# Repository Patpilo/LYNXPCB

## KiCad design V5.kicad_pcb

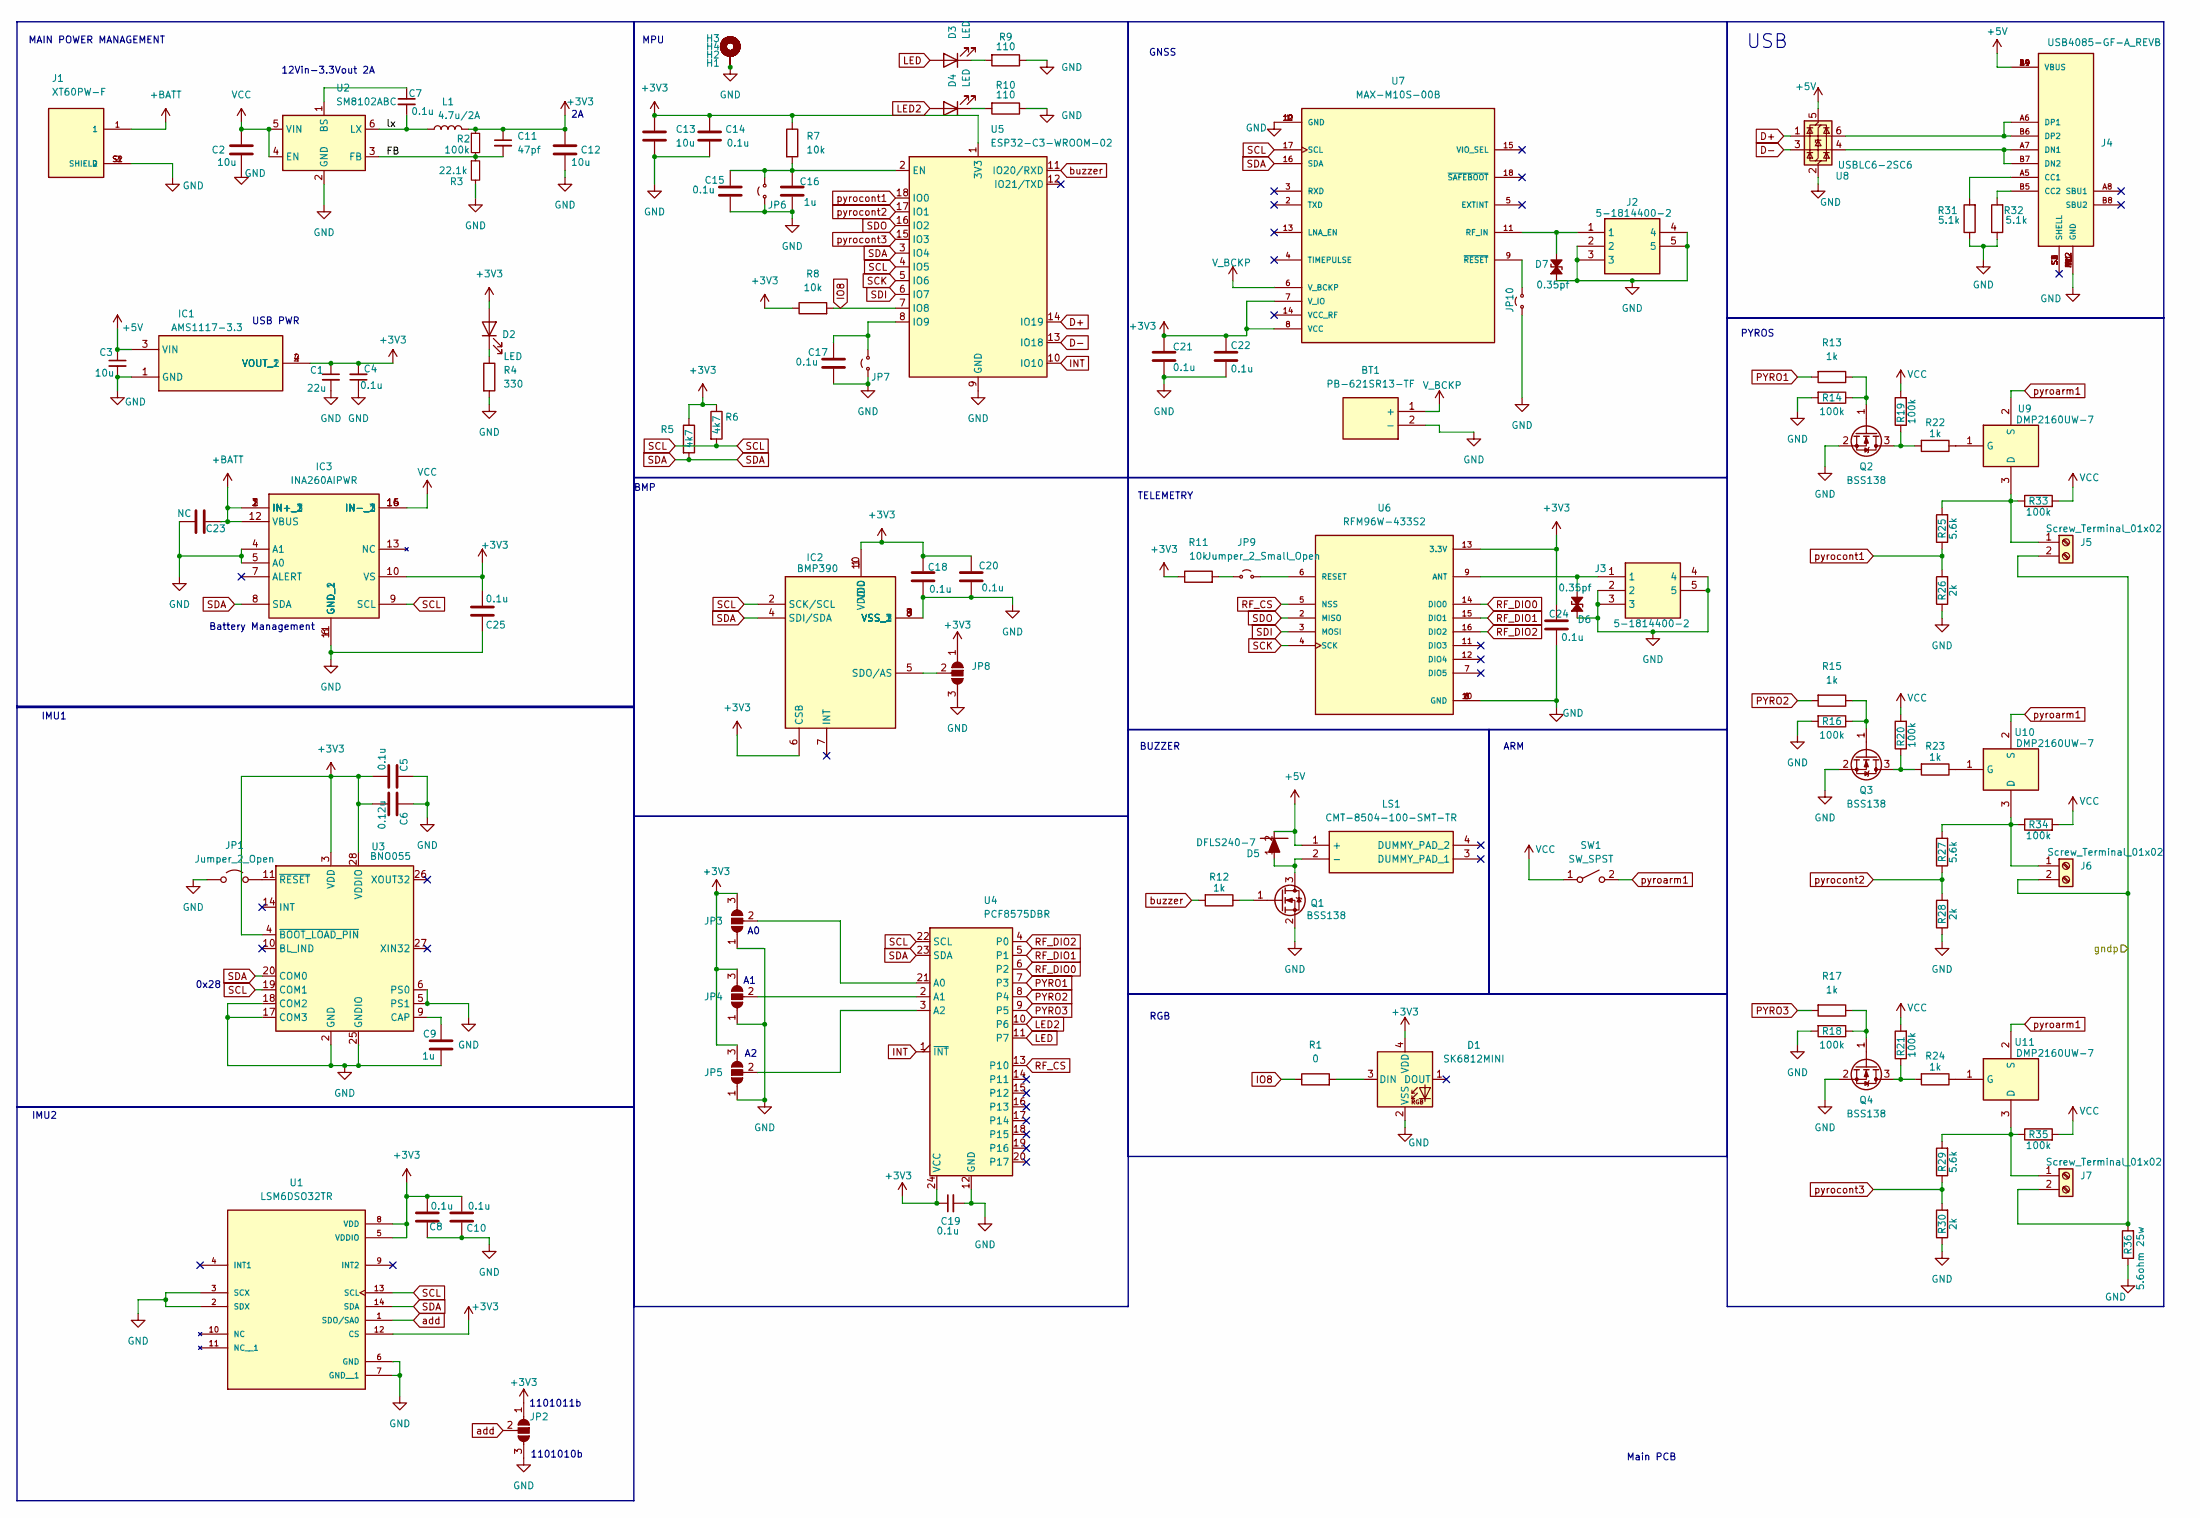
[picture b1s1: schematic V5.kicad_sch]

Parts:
BT1: PB-621SR13-TF; PB621SR13TF; Manufacturer_Part_Number PB-621SR13-TF
C1: 22u; C_0805_2012Metric_Pad1.18x1.45mm_HandSolder
C2, C12: 10u; C_1206_3216Metric_Pad1.33x1.80mm_HandSolder
C3, C13: 10u; C_0805_2012Metric_Pad1.18x1.45mm_HandSolder
C4, C7, C15, C17, C18, C19, C20, C21, C22: 0.1u; C_0805_2012Metric_Pad1.18x1.45mm_HandSolder
C5, C8, C10, C14, C25: 0.1u; C_0201_0603Metric_Pad0.64x0.40mm_HandSolder
C6: 0.12u; C_0201_0603Metric_Pad0.64x0.40mm_HandSolder
C9, C16: 1u; C_0805_2012Metric_Pad1.18x1.45mm_HandSolder
C11: 47pf; C_0402_1005Metric_Pad0.74x0.62mm_HandSolder
C23: NC; C_0201_0603Metric_Pad0.64x0.40mm_HandSolder
C24: 0.1u; C_1206_3216Metric_Pad1.33x1.80mm_HandSolder
D1: SK6812MINI; LED_SK6812MINI_PLCC4_3.5x3.5mm_P1.75mm
D2, D3, D4: LED; LED_0805_2012Metric_Pad1.15x1.40mm_HandSolder
D5: DFLS240-7; POWERDI123; Manufacturer_Part_Number DFLS240-7; Mouser Part Number 621-DFLS240-7
D6, D7: 0.35pf; D_01005_0402Metric_Pad0.57x0.30mm_HandSolder
H1, H2, H3, H4: MountingHole_Pad; MountingHole_2.7mm_M2.5_Pad_Via
IC1: AMS1117-3.3; SOT229P700X180-4N; Manufacturer_Part_Number AMS1117-3.3
IC2: BMP390; Manufacturer_Part_Number BMP390; Mouser Part Number 262-BMP390
IC3: INA260AIPWR; SOP65P640X120-16N; Manufacturer_Part_Number INA260AIPWR; Mouser Part Number 595-INA260AIPWR
J1: XT60PW-F; AMASS_XT60PW-F; PARTREV V1.2
J2, J3: 5-1814400-2; 518144002; Manufacturer_Part_Number 5-1814400-2; Mouser Part Number 571-5-1814400-2
J4: USB4085-GF-A_REVB; GCT_USB4085-GF-A_REVB; PARTREV B
J5, J6, J7: Screw_Terminal_01x02; 2828362
JP1: Jumper_2_Open; SolderJumper-2_P1.3mm_Open_RoundedPad1.0x1.5mm
JP2, JP3, JP4, JP5, JP8: SolderJumper_3_Open; SolderJumper-3_P1.3mm_Open_RoundedPad1.0x1.5mm_NumberLabels
JP6, JP7, JP9, JP10: Jumper_2_Small_Open; SolderJumper-2_P1.3mm_Open_RoundedPad1.0x1.5mm
L1: 4.7u/2A; 74438357100
LS1: CMT-8504-100-SMT-TR; CMT8504100SMTTR; Manufacturer_Part_Number CMT-8504-100-SMT-TR; Mouser Part Number 490-CMT-8504100SMTTR
Q1, Q2, Q3, Q4: BSS138; SOT-23
R1: 0; R_0805_2012Metric_Pad1.20x1.40mm_HandSolder
R2: 100k; R_0402_1005Metric_Pad0.72x0.64mm_HandSolder
R3: 22.1k; R_0402_1005Metric_Pad0.72x0.64mm_HandSolder
R4: 330; R_0805_2012Metric_Pad1.20x1.40mm_HandSolder
R5, R6: 4k7; R_0805_2012Metric_Pad1.20x1.40mm_HandSolder
R7, R8, R11: 10k; R_0805_2012Metric_Pad1.20x1.40mm_HandSolder
R9, R10: 110; R_0805_2012Metric_Pad1.20x1.40mm_HandSolder
R12: 1k; R_0805_2012Metric_Pad1.20x1.40mm_HandSolder
R13, R15, R17, R22, R23, R24: 1k; R_0402_1005Metric_Pad0.72x0.64mm_HandSolder
R14, R16, R18, R19, R20, R21: 100k; R_0805_2012Metric_Pad1.20x1.40mm_HandSolder
R25, R27, R29: 5.6k; R_0402_1005Metric_Pad0.72x0.64mm_HandSolder
R26, R28, R30: 2k; R_0402_1005Metric_Pad0.72x0.64mm_HandSolder
R31, R32: 5.1k; R_0402_1005Metric_Pad0.72x0.64mm_HandSolder
R33, R34, R35: 100k; R_0603_1608Metric_Pad0.98x0.95mm_HandSolder
R36: 5.6ohm 25w; TO-263-2_TabPin1
SW1: SW_SPST; MN11LL1W01-C
U1: LSM6DSO32TR; LGA-14L_2P5X3X0P83_STM; PARTREV 1
U2: SM8102ABC; SOT-23-6
U3: BNO055; LGA-28_5.2x3.8mm_P0.5mm
U4: PCF8575DBR; SSOP-24_5.3x8.2mm_P0.65mm
U5: ESP32-C3-WROOM-02
U6: RFM96W-433S2; MODULE_RFM96W-433S2; PARTREV 2.0
U7: MAX-M10S-00B; XCVR_MAX-M10S-00B; PARTREV C1
U8: USBLC6-2SC6; SOT-23-6
U9, U10, U11: DMP2160UW-7; SOT-323_SC-70; Manufacturer_Part_Number DMP2160UW-7; Mouser Part Number 621-DMP2160UW-7

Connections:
+3V3: C1.1, C4.2, C5.1, C6.1, C8.1, C10.1, C11.1, C12.1, C13.1, C14.1, C18.1, C19.1, C20.1, C21.1, C22.1, C24.1, C25.1, D1.4 (VDD), D2.2 (A), IC1.2 (VOUT_1), IC1.4 (VOUT_2), IC2.1 (VDDIO), IC2.6 (CSB), IC2.10 (VDD), IC3.10 (VS), JP2.1 (A), JP3.3 (B), JP4.3 (B), JP5.3 (B), JP8.1 (A), L1.2, R2.1, R5.1, R6.1, R7.1, R8.1, R11.1, U1.5 (VDDIO), U1.8 (VDD), U1.12 (CS), U3.3 (VDD), U3.4 (~BOOT_LOAD_PIN), U3.28 (VDDIO), U4.24 (VCC), U5.1 (3V3), U6.13 (3.3V), U7.7 (V_IO), U7.8 (VCC)
+5V: C3.1, D5.2 (K), IC1.3 (VIN), J4.A4 (VBUS), J4.A9 (VBUS), J4.B4 (VBUS), J4.B9 (VBUS), LS1.1 (+), U8.5 (VBUS)
+BATT: C23.2, IC3.1 (IN+_1), IC3.2 (IN+_2), IC3.3 (IN+_3), IC3.12 (VBUS), J1.1
/FB: C11.2, R2.2, R3.1, U2.3 (FB)
/gndp: J5.2, J6.2, J7.2, R36.2
/lx: C7.2, L1.1, U2.6 (LX)
D+: U5.14 (IO19), U8.1 (I/O1)
D-: U5.13 (IO18), U8.3 (I/O2)
GND: BT1.2 (-), C1.2, C2.2, C3.2, C4.1, C5.2, C6.2, C8.2, C9.1, C10.2, C12.2, C13.2, C14.2, C15.2, C16.2, C17.2, C18.2, C19.2, C20.2, C21.2, C22.2, C23.1, C24.2, C25.2, D1.2 (VSS), D6.1 (A1), D7.1 (A1), H1.1, H2.1, H3.1, H4.1, IC1.1 (GND), IC2.3 (VSS_1), IC2.8 (VSS_2), IC2.9 (VSS_3), IC3.4 (A1), IC3.5 (A0), IC3.6 (GND_1), IC3.11 (GND_2), J1.2, J1.S1 (SHIELD), J1.S2 (SHIELD), J2.2, J2.3, J2.4, J2.5, J3.2, J3.3, J3.4, J3.5, J4.A1 (GND), J4.A12 (GND), J4.B1 (GND), J4.B12 (GND), JP1.1 (A), JP2.3 (B), JP3.1 (A), JP4.1 (A), JP5.1 (A), JP6.1 (A), JP7.1 (A), JP8.3 (B), JP10.1 (A), Q1.2 (S), Q2.2 (S), Q3.2 (S), Q4.2 (S), R3.2, R4.2, R9.1, R10.1, R14.2, R16.2, R18.2, R26.1, R28.1, R30.1, R31.1, R32.1, R36.1, U1.2 (SDX), U1.3 (SCX), U1.6 (GND), U1.7 (GND__1), U2.2 (GND), U3.2 (GND), U3.5 (PS1), U3.6 (PS0), U3.17 (COM3), U3.18 (COM2), U3.25 (GNDIO), U4.12 (GND), U5.9 (GND), U5.19 (GND), U6.1 (GND), U6.8 (GND), U6.10 (GND), U7.1 (GND), U7.10 (GND), U7.12 (GND), U8.2 (GND)
INT: U4.1 (~INT), U5.10 (IO10)
IO8: R1.1, R8.2, U5.7 (IO8)
LED: D3.2 (A), U4.11 (P7)
LED2: D4.2 (A), U4.10 (P6)
unnamed: D1.3 (DIN), R1.2
unnamed: D2.1 (K), R4.1
unnamed: D3.1 (K), R9.2
unnamed: D4.1 (K), R10.2
unnamed: D5.1 (A), LS1.2 (-), Q1.3 (D)
unnamed: D6.2 (A2), J3.1, U6.9 (ANT)
unnamed: D7.2 (A2), J2.1, U7.11 (RF_IN)
unnamed: IC2.5 (SDO/AS), JP8.2 (C)
unnamed: J4.A5 (CC1), R31.2
unnamed: J4.B5 (CC2), R32.2
unnamed: J4.A7 (DN1), J4.B7 (DN2), U8.4 (I/O2)
unnamed: J4.A6 (DP1), J4.B6 (DP2), U8.6 (I/O1)
unnamed: J5.1, R25.2, R33.1, U9.3 (D)
unnamed: J6.1, R27.2, R34.1, U10.3 (D)
unnamed: J7.1, R29.2, R35.1, U11.3 (D)
unnamed: JP1.2 (B), U3.11 (~RESET)
unnamed: JP3.2 (C), U4.21 (A0)
unnamed: JP4.2 (C), U4.2 (A1)
unnamed: JP5.2 (C), U4.3 (A2)
unnamed: C15.1, C16.1, JP6.2 (B), R7.2, U5.2 (EN)
unnamed: C17.1, JP7.2 (B), U5.8 (IO9)
unnamed: JP9.1 (A), R11.2
unnamed: JP9.2 (B), U6.6 (RESET)
unnamed: JP10.2 (B), U7.9 (~RESET)
unnamed: Q1.1 (G), R12.1
unnamed: Q2.3 (D), R19.1, R22.2
unnamed: Q2.1 (G), R13.1, R14.1
unnamed: Q3.3 (D), R20.1, R23.2
unnamed: Q3.1 (G), R15.1, R16.1
unnamed: Q4.3 (D), R21.1, R24.2
unnamed: Q4.1 (G), R17.1, R18.1
unnamed: C7.1, U2.1 (BS)
unnamed: C9.2, U3.9 (CAP)
unnamed: R22.1, U9.1 (G)
unnamed: R23.1, U10.1 (G)
unnamed: R24.1, U11.1 (G)
PYRO1: R13.2, U4.7 (P3)
PYRO2: R15.2, U4.8 (P4)
PYRO3: R17.2, U4.9 (P5)
RF_CS: U4.13 (P10), U6.5 (NSS)
RF_DIO0: U4.6 (P2), U6.14 (DIO0)
RF_DIO1: U4.5 (P1), U6.15 (DIO1)
RF_DIO2: U4.4 (P0), U6.16 (DIO2)
SCK: U5.5 (IO6), U6.4 (SCK)
SCL: IC2.2 (SCK/SCL), IC3.9 (SCL), R6.2, U1.13 (SCL), U3.19 (COM1), U4.22 (SCL), U5.4 (IO5), U7.17 (SCL)
SDA: IC2.4 (SDI/SDA), IC3.8 (SDA), R5.2, U1.14 (SDA), U3.20 (COM0), U4.23 (SDA), U5.3 (IO4), U7.16 (SDA)
SDI: U5.6 (IO7), U6.3 (MOSI)
SDO: U5.16 (IO2), U6.2 (MISO)
VCC: C2.1, IC3.14 (IN-_1), IC3.15 (IN-_2), IC3.16 (IN-_3), R19.2, R20.2, R21.2, R33.2, R34.2, R35.2, SW1.1 (A), U2.4 (EN), U2.5 (VIN)
V_BCKP: BT1.1 (+), U7.6 (V_BCKP)
add: JP2.2 (C), U1.1 (SDO/SA0)
buzzer: R12.2, U5.11 (IO20/RXD)
pyroarm1: SW1.2 (B), U9.2 (S), U10.2 (S), U11.2 (S)
pyrocont1: R25.1, R26.2, U5.18 (IO0)
pyrocont2: R27.1, R28.2, U5.17 (IO1)
pyrocont3: R29.1, R30.2, U5.15 (IO3)

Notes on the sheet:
IMU2
0x28
1101010b
MPU
PYROS
ARM
12Vin-3.3Vout 2A
Main PCB
IMU1
Battery Management
USB PWR
BMP
TELEMETRY
GNSS
BUZZER
1101011b
RGB
MAIN POWER MANAGEMENT
USB

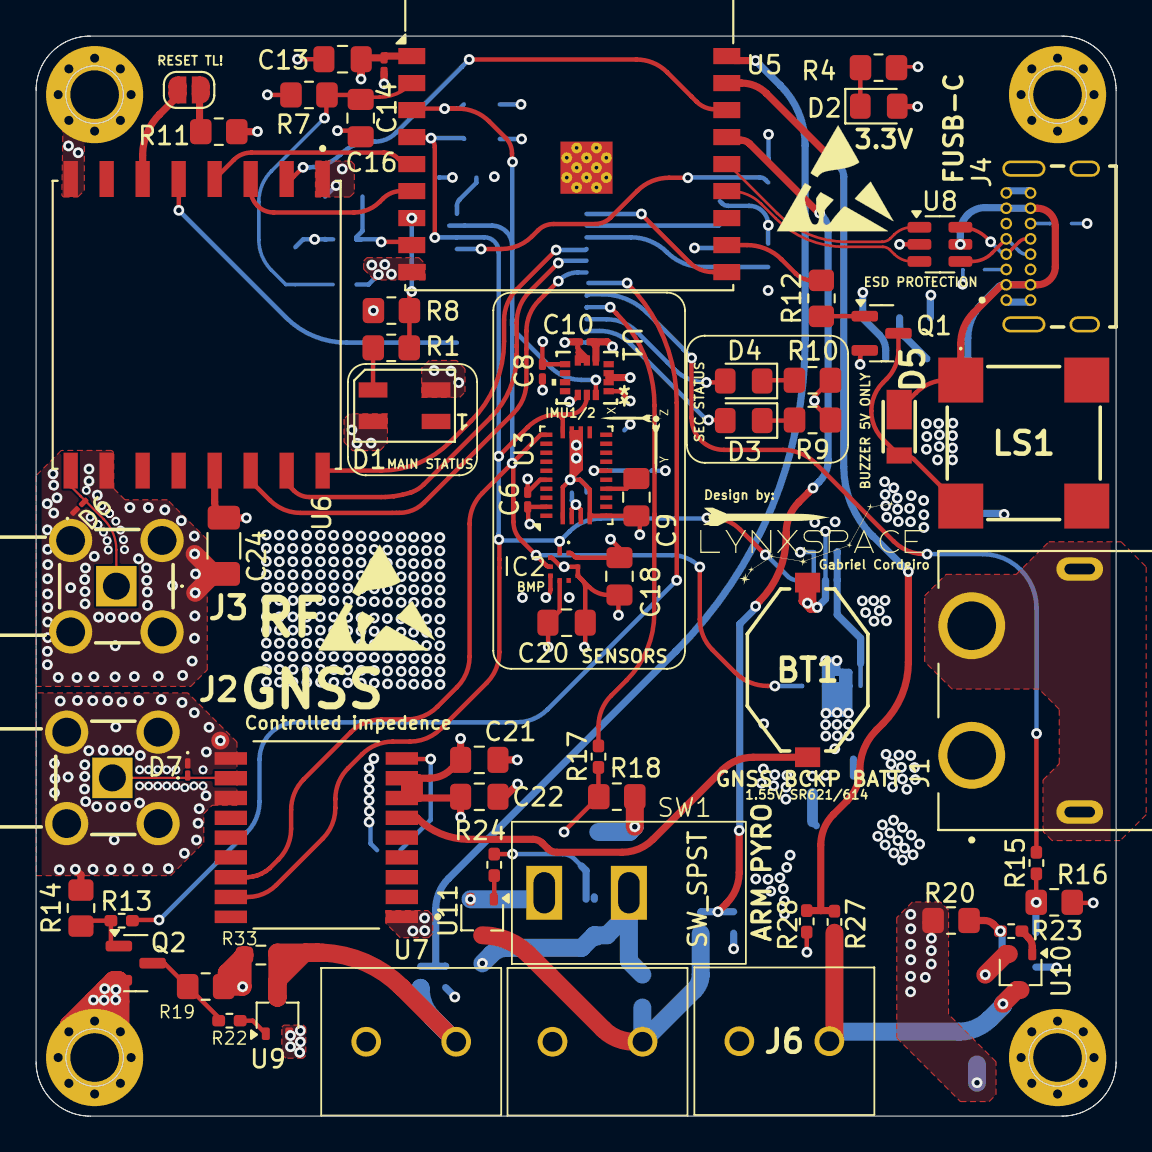
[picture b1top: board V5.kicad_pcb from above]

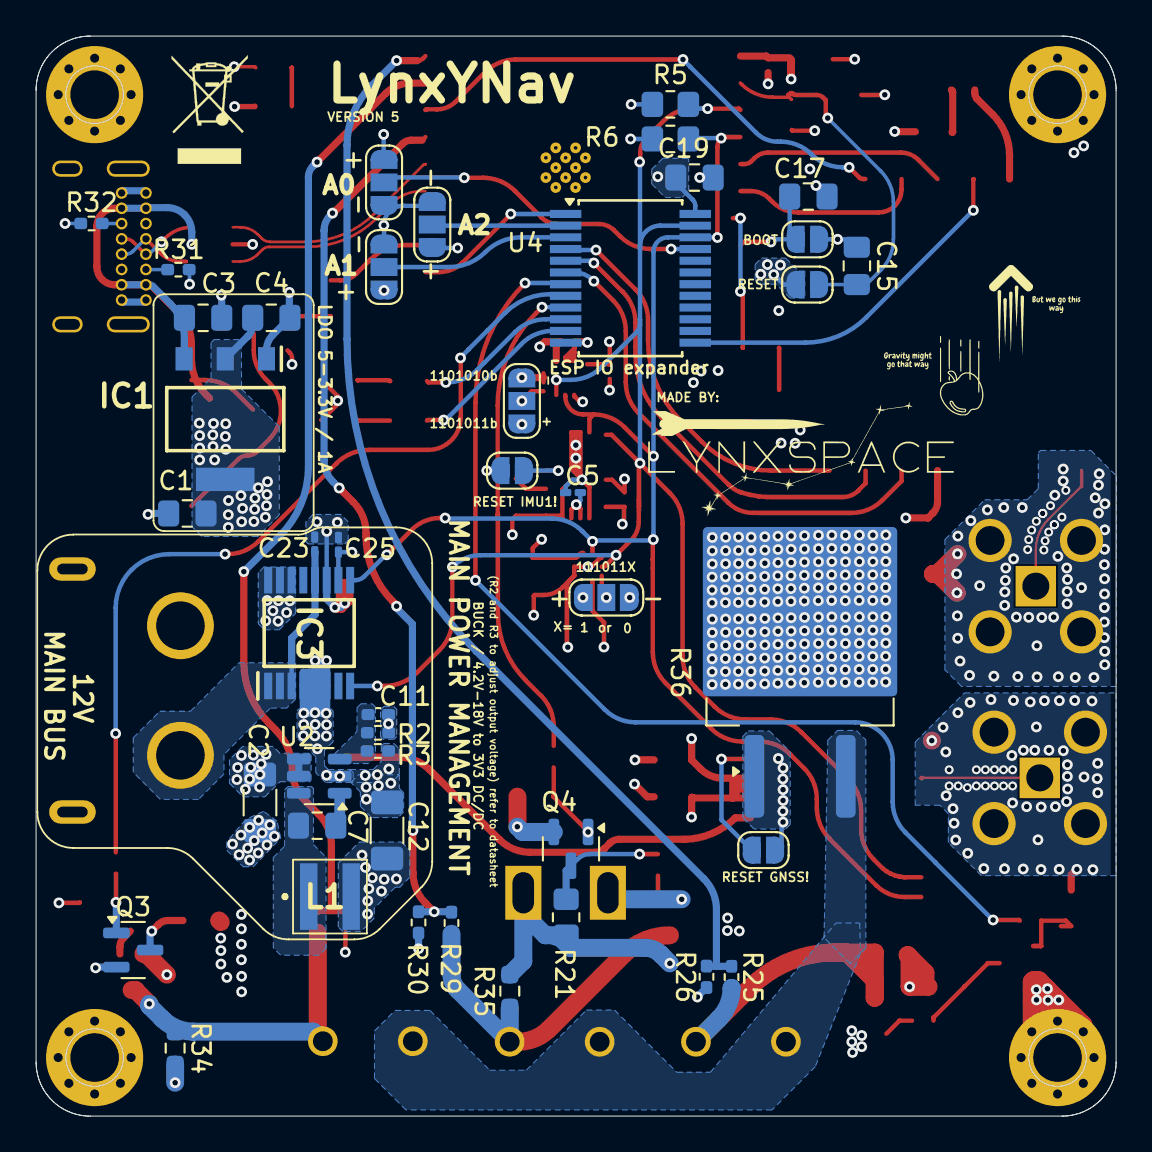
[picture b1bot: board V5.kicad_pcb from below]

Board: 4 copper layers, 60.0 x 60.0 mm, 111 parts (43 on the bottom side), 69 nets.
